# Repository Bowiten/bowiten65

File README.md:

# bowiten65
a 65% keyboard pcb with a jst connector for a [unified daughterboard](https://github.com/Unified-Daughterboard/Unified-Daughterboard)
# layout

# kicad renders

# production
i have sent this to jlcpcb to make, although it hasn't arrived yet, so use at your own risk

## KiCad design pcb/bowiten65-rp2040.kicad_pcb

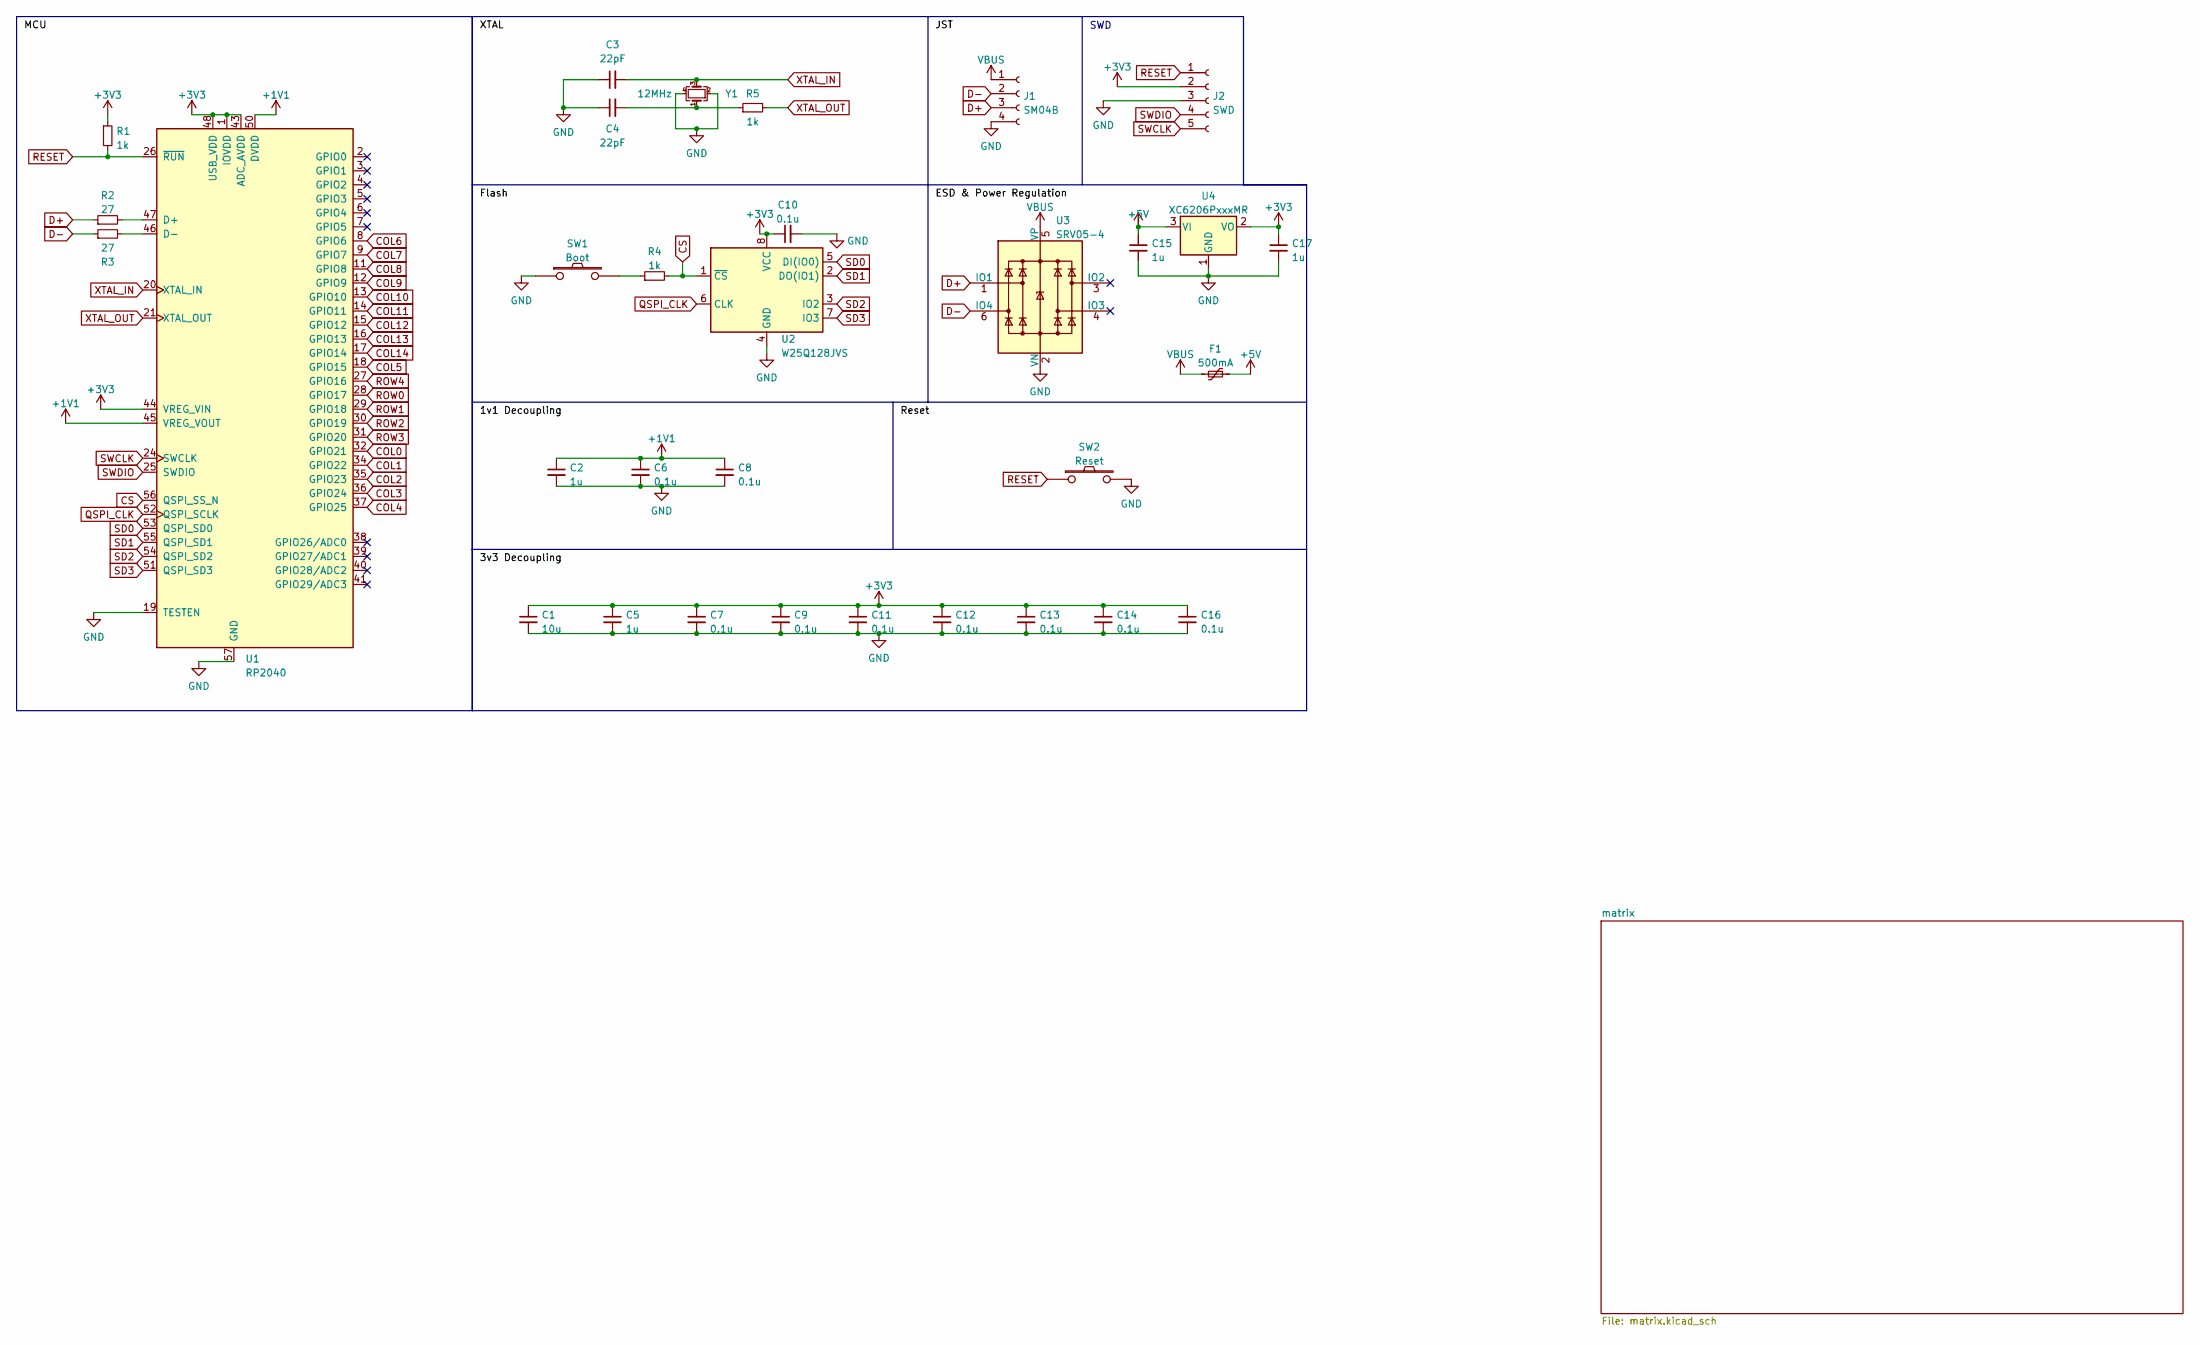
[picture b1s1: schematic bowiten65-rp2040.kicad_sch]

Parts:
C1: 10u; C_0402_1005Metric
C2, C5, C15, C17: 1u; C_0402_1005Metric
C3, C4: 22pF; C_0402_1005Metric
C6, C7, C8, C9, C10, C11, C12, C13, C14, C16: 0.1u; C_0402_1005Metric
F1: 500mA; Fuse_1206_3216Metric
J1: SM04B; JST_SH_SM04B-SRSS-TB_1x04-1MP_P1.00mm_Horizontal
J2: SWD; PinSocket_1x05_P2.54mm_Vertical
R1, R4, R5: 1k; R_0402_1005Metric
R2, R3: 27; R_0603_1608Metric
SW1: Boot; SW_SPST_TL3342
SW2: Reset; SW_SPST_TL3342
U1: RP2040; RP2040-QFN-56; LCSC C2040
U2: W25Q128JVS; SOIC-8_5.23x5.23mm_P1.27mm
U3: SRV05-4; SOT-23-6-routable
U4: XC6206PxxxMR; SOT-23
Y1: 12MHz; Crystal_SMD_3225-4Pin_3.2x2.5mm

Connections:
+1V1: C2.1, C6.1, C8.1, U1.23 (DVDD), U1.45 (VREG_VOUT), U1.50 (DVDD)
+3V3: C1.1, C5.1, C7.1, C9.1, C10.1, C11.1, C12.1, C13.1, C14.1, C16.1, C17.1, J2.2, R1.1, U1.1 (IOVDD), U1.10 (IOVDD), U1.22 (IOVDD), U1.33 (IOVDD), U1.42 (IOVDD), U1.43 (ADC_AVDD), U1.44 (VREG_VIN), U1.48 (USB_VDD), U1.49 (IOVDD), U2.8 (VCC), U4.2 (VO)
+5V: C15.1, F1.1, U4.3 (VI)
COL0: U1.32 (GPIO21); also elsewhere on the board
COL1: U1.34 (GPIO22); also elsewhere on the board
COL2: U1.35 (GPIO23); also elsewhere on the board
COL3: U1.36 (GPIO24); also elsewhere on the board
COL4: U1.37 (GPIO25); also elsewhere on the board
COL5: U1.18 (GPIO15); also elsewhere on the board
COL6: U1.8 (GPIO6); also elsewhere on the board
COL7: U1.9 (GPIO7); also elsewhere on the board
COL8: U1.11 (GPIO8); also elsewhere on the board
COL9: U1.12 (GPIO9); also elsewhere on the board
COL10: U1.13 (GPIO10); also elsewhere on the board
COL11: U1.14 (GPIO11); also elsewhere on the board
COL12: U1.15 (GPIO12); also elsewhere on the board
COL13: U1.16 (GPIO13); also elsewhere on the board
COL14: U1.17 (GPIO14); also elsewhere on the board
CS: R4.2, U1.56 (QSPI_SS_N), U2.1 (~CS)
D+: J1.3, R2.1, U3.1 (IO1)
D-: J1.2, R3.1, U3.6 (IO4)
GND: C1.2, C2.2, C3.1, C4.1, C5.2, C6.2, C7.2, C8.2, C9.2, C10.2, C11.2, C12.2, C13.2, C14.2, C15.2, C16.2, C17.2, J1.4, J2.3, SW1.1, SW2.2, U1.19 (TESTEN), U1.57 (GND), U2.4 (GND), U3.2 (VN), U4.1 (GND), Y1.2, Y1.4
unnamed: C4.2, R5.1, Y1.1
unnamed: R2.2, U1.47 (D+)
unnamed: R3.2, U1.46 (D-)
unnamed: R4.1, SW1.2
QSPI_CLK: U1.52 (QSPI_SCLK), U2.6 (CLK)
RESET: J2.1, R1.2, SW2.1, U1.26 (~RUN)
ROW0: U1.28 (GPIO17); also elsewhere on the board
ROW1: U1.29 (GPIO18); also elsewhere on the board
ROW2: U1.30 (GPIO19); also elsewhere on the board
ROW3: U1.31 (GPIO20); also elsewhere on the board
ROW4: U1.27 (GPIO16); also elsewhere on the board
SD0: U1.53 (QSPI_SD0), U2.5 (DI(IO0))
SD1: U1.55 (QSPI_SD1), U2.2 (DO(IO1))
SD2: U1.54 (QSPI_SD2), U2.3 (IO2)
SD3: U1.51 (QSPI_SD3), U2.7 (IO3)
SWCLK: J2.5, U1.24 (SWCLK)
SWDIO: J2.4, U1.25 (SWDIO)
VBUS: F1.2, J1.1, U3.5 (VP)
XTAL_IN: C3.2, U1.20 (XTAL_IN), Y1.3
XTAL_OUT: R5.2, U1.21 (XTAL_OUT)

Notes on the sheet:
SWD

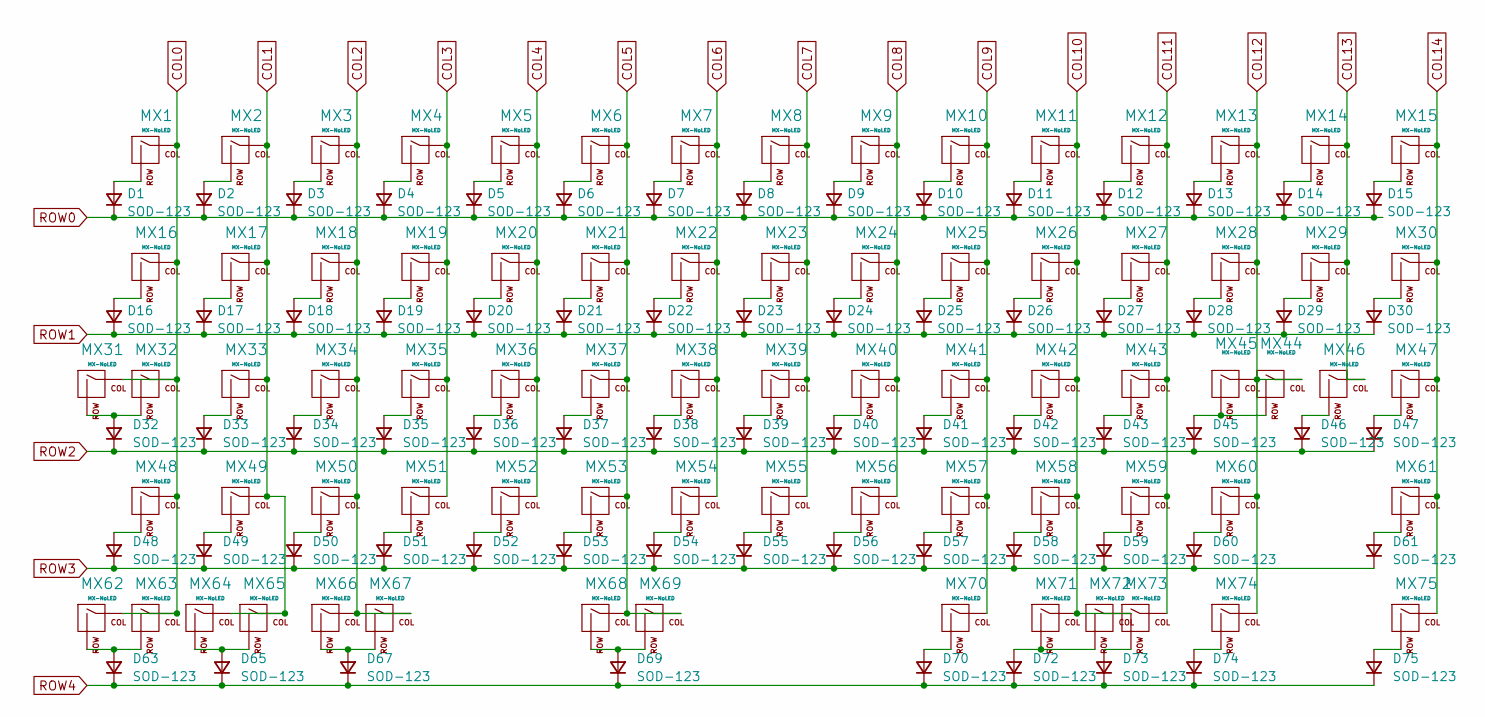
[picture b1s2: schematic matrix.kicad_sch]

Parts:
D1, D2, D3, D4, D5, D6, D7, D8, D9, D10, D11, D12, D13, D14, D15, D16, D17, D18, D19, D20, D21, D22, D23, D24, D25, D26, D27, D28, D29, D30, D32, D33, D34, D35, D36, D37, D38, D39, D40, D41, D42, D43, D45, D46, D47, D48, D49, D50, D51, D52, D53, D54, D55, D56, D57, D58, D59, D60, D61, D63, D65, D67, D69, D70, D72, D73, D74, D75: SOD-123; D_SOD-123; LCSC C33221
MX1, MX2, MX3, MX4, MX5, MX6, MX7, MX8, MX9, MX10, MX11, MX12, MX13, MX15, MX17, MX18, MX19, MX20, MX21, MX22, MX23, MX24, MX25, MX26, MX27, MX28, MX30, MX33, MX34, MX35, MX36, MX37, MX38, MX39, MX40, MX41, MX42, MX43, MX44, MX47, MX49, MX50, MX51, MX52, MX53, MX54, MX55, MX56, MX57, MX58, MX60, MX61, MX65, MX73, MX74, MX75: MX-NoLED; MXOnly-1U-NoLED
MX14: MX-NoLED; MXOnly-2U-NoLED
MX16, MX29, MX63, MX67, MX71: MX-NoLED; MXOnly-1.5U-NoLED
MX31, MX46, MX62, MX64, MX66, MX70, MX72: MX-NoLED; MXOnly-1.25U-NoLED
MX32, MX59: MX-NoLED; MXOnly-1.75U-NoLED
MX45, MX48: MX-NoLED; MXOnly-2.25U-NoLED
MX68: MX-NoLED; MXOnly-6.25U-ReversedStabilizers-NoLED
MX69: MX-NoLED; MXOnly-7U-ReversedStabilizers-NoLED

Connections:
COL0: MX1.1 (COL), MX16.1 (COL), MX31.1 (COL), MX32.1 (COL), MX48.1 (COL), MX62.1 (COL), MX63.1 (COL); also elsewhere on the board
COL1: MX2.1 (COL), MX17.1 (COL), MX33.1 (COL), MX49.1 (COL), MX64.1 (COL), MX65.1 (COL); also elsewhere on the board
COL2: MX3.1 (COL), MX18.1 (COL), MX34.1 (COL), MX50.1 (COL), MX66.1 (COL), MX67.1 (COL); also elsewhere on the board
COL3: MX4.1 (COL), MX19.1 (COL), MX35.1 (COL), MX51.1 (COL); also elsewhere on the board
COL4: MX5.1 (COL), MX20.1 (COL), MX36.1 (COL), MX52.1 (COL); also elsewhere on the board
COL5: MX6.1 (COL), MX21.1 (COL), MX37.1 (COL), MX53.1 (COL), MX68.1 (COL), MX69.1 (COL); also elsewhere on the board
COL6: MX7.1 (COL), MX22.1 (COL), MX38.1 (COL), MX54.1 (COL); also elsewhere on the board
COL7: MX8.1 (COL), MX23.1 (COL), MX39.1 (COL), MX55.1 (COL); also elsewhere on the board
COL8: MX9.1 (COL), MX24.1 (COL), MX40.1 (COL), MX56.1 (COL); also elsewhere on the board
COL9: MX10.1 (COL), MX25.1 (COL), MX41.1 (COL), MX57.1 (COL), MX70.1 (COL); also elsewhere on the board
COL10: MX11.1 (COL), MX26.1 (COL), MX42.1 (COL), MX58.1 (COL), MX71.1 (COL), MX72.1 (COL); also elsewhere on the board
COL11: MX12.1 (COL), MX27.1 (COL), MX43.1 (COL), MX59.1 (COL), MX73.1 (COL); also elsewhere on the board
COL12: MX13.1 (COL), MX28.1 (COL), MX44.1 (COL), MX45.1 (COL), MX60.1 (COL), MX74.1 (COL); also elsewhere on the board
COL13: MX14.1 (COL), MX29.1 (COL), MX46.1 (COL); also elsewhere on the board
COL14: MX15.1 (COL), MX30.1 (COL), MX47.1 (COL), MX61.1 (COL), MX75.1 (COL); also elsewhere on the board
unnamed: D1.2 (A), MX1.2 (ROW)
unnamed: D2.2 (A), MX2.2 (ROW)
unnamed: D3.2 (A), MX3.2 (ROW)
unnamed: D4.2 (A), MX4.2 (ROW)
unnamed: D5.2 (A), MX5.2 (ROW)
unnamed: D6.2 (A), MX6.2 (ROW)
unnamed: D7.2 (A), MX7.2 (ROW)
unnamed: D8.2 (A), MX8.2 (ROW)
unnamed: D9.2 (A), MX9.2 (ROW)
unnamed: D10.2 (A), MX10.2 (ROW)
unnamed: D11.2 (A), MX11.2 (ROW)
unnamed: D12.2 (A), MX12.2 (ROW)
unnamed: D13.2 (A), MX13.2 (ROW)
unnamed: D14.2 (A), MX14.2 (ROW)
unnamed: D15.2 (A), MX15.2 (ROW)
unnamed: D16.2 (A), MX16.2 (ROW)
unnamed: D17.2 (A), MX17.2 (ROW)
unnamed: D18.2 (A), MX18.2 (ROW)
unnamed: D19.2 (A), MX19.2 (ROW)
unnamed: D20.2 (A), MX20.2 (ROW)
unnamed: D21.2 (A), MX21.2 (ROW)
unnamed: D22.2 (A), MX22.2 (ROW)
unnamed: D23.2 (A), MX23.2 (ROW)
unnamed: D24.2 (A), MX24.2 (ROW)
unnamed: D25.2 (A), MX25.2 (ROW)
unnamed: D26.2 (A), MX26.2 (ROW)
unnamed: D27.2 (A), MX27.2 (ROW)
unnamed: D28.2 (A), MX28.2 (ROW)
unnamed: D29.2 (A), MX29.2 (ROW)
unnamed: D30.2 (A), MX30.2 (ROW)
unnamed: D32.2 (A), MX31.2 (ROW), MX32.2 (ROW)
unnamed: D33.2 (A), MX33.2 (ROW)
unnamed: D34.2 (A), MX34.2 (ROW)
unnamed: D35.2 (A), MX35.2 (ROW)
unnamed: D36.2 (A), MX36.2 (ROW)
unnamed: D37.2 (A), MX37.2 (ROW)
unnamed: D38.2 (A), MX38.2 (ROW)
unnamed: D39.2 (A), MX39.2 (ROW)
unnamed: D40.2 (A), MX40.2 (ROW)
unnamed: D41.2 (A), MX41.2 (ROW)
unnamed: D42.2 (A), MX42.2 (ROW)
unnamed: D43.2 (A), MX43.2 (ROW)
unnamed: D45.2 (A), MX44.2 (ROW), MX45.2 (ROW)
unnamed: D46.2 (A), MX46.2 (ROW)
unnamed: D47.2 (A), MX47.2 (ROW)
unnamed: D48.2 (A), MX48.2 (ROW)
unnamed: D49.2 (A), MX49.2 (ROW)
unnamed: D50.2 (A), MX50.2 (ROW)
unnamed: D51.2 (A), MX51.2 (ROW)
unnamed: D52.2 (A), MX52.2 (ROW)
unnamed: D53.2 (A), MX53.2 (ROW)
unnamed: D54.2 (A), MX54.2 (ROW)
unnamed: D55.2 (A), MX55.2 (ROW)
unnamed: D56.2 (A), MX56.2 (ROW)
unnamed: D57.2 (A), MX57.2 (ROW)
unnamed: D58.2 (A), MX58.2 (ROW)
unnamed: D59.2 (A), MX59.2 (ROW)
unnamed: D60.2 (A), MX60.2 (ROW)
unnamed: D61.2 (A), MX61.2 (ROW)
unnamed: D63.2 (A), MX62.2 (ROW), MX63.2 (ROW)
unnamed: D65.2 (A), MX64.2 (ROW), MX65.2 (ROW)
unnamed: D67.2 (A), MX66.2 (ROW), MX67.2 (ROW)
unnamed: D69.2 (A), MX68.2 (ROW), MX69.2 (ROW)
unnamed: D70.2 (A), MX70.2 (ROW)
unnamed: D72.2 (A), MX71.2 (ROW), MX72.2 (ROW)
unnamed: D73.2 (A), MX73.2 (ROW)
unnamed: D74.2 (A), MX74.2 (ROW)
unnamed: D75.2 (A), MX75.2 (ROW)
ROW0: D1.1 (K), D2.1 (K), D3.1 (K), D4.1 (K), D5.1 (K), D6.1 (K), D7.1 (K), D8.1 (K), D9.1 (K), D10.1 (K), D11.1 (K), D12.1 (K), D13.1 (K), D14.1 (K), D15.1 (K); also elsewhere on the board
ROW1: D16.1 (K), D17.1 (K), D18.1 (K), D19.1 (K), D20.1 (K), D21.1 (K), D22.1 (K), D23.1 (K), D24.1 (K), D25.1 (K), D26.1 (K), D27.1 (K), D28.1 (K), D29.1 (K), D30.1 (K); also elsewhere on the board
ROW2: D32.1 (K), D33.1 (K), D34.1 (K), D35.1 (K), D36.1 (K), D37.1 (K), D38.1 (K), D39.1 (K), D40.1 (K), D41.1 (K), D42.1 (K), D43.1 (K), D45.1 (K), D46.1 (K), D47.1 (K); also elsewhere on the board
ROW3: D48.1 (K), D49.1 (K), D50.1 (K), D51.1 (K), D52.1 (K), D53.1 (K), D54.1 (K), D55.1 (K), D56.1 (K), D57.1 (K), D58.1 (K), D59.1 (K), D60.1 (K), D61.1 (K); also elsewhere on the board
ROW4: D63.1 (K), D65.1 (K), D67.1 (K), D69.1 (K), D70.1 (K), D72.1 (K), D73.1 (K), D74.1 (K), D75.1 (K); also elsewhere on the board

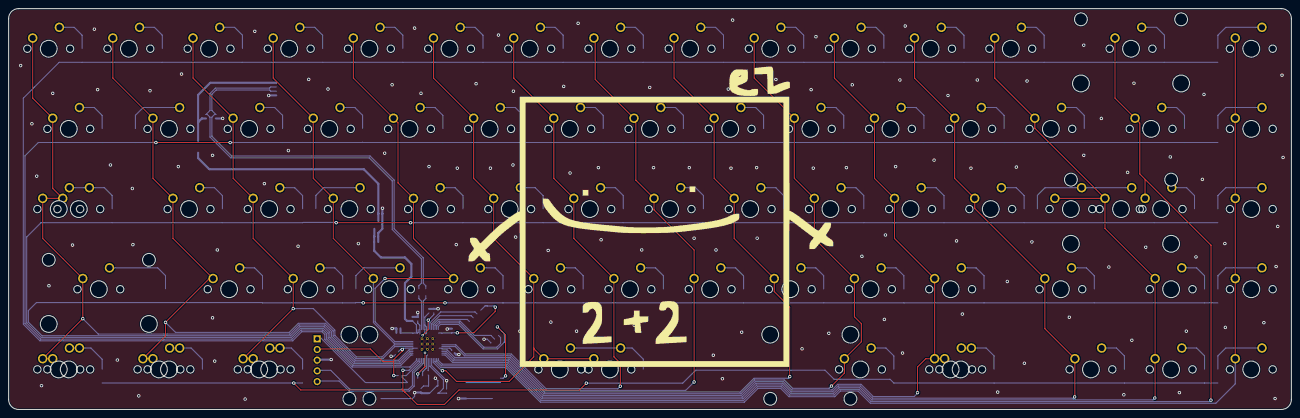
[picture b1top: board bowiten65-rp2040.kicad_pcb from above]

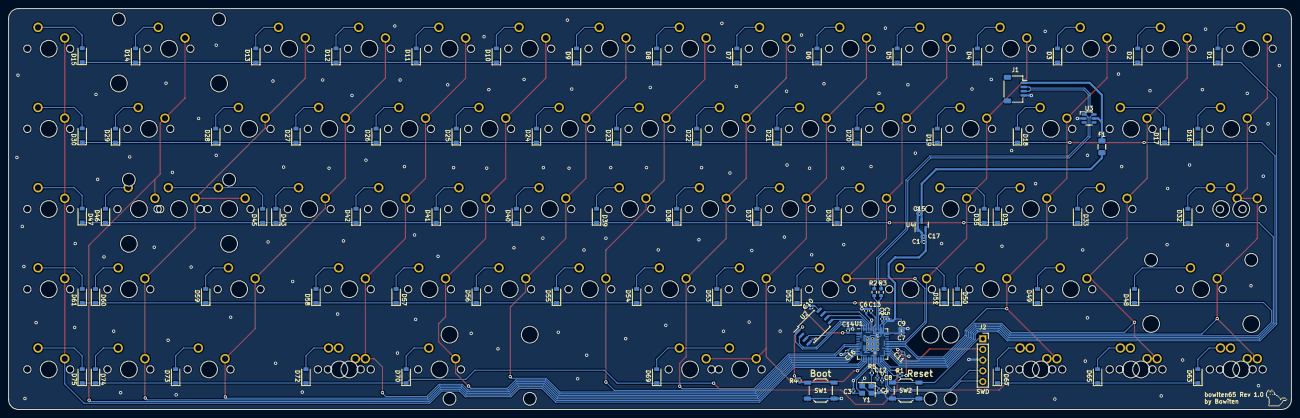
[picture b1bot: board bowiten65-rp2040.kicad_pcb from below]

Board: 2 copper layers, 304.8 x 95.2 mm, 175 parts (100 on the bottom side), 110 nets.

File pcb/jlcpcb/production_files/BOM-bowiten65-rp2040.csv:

Comment,Designator,Footprint,LCSC
1k,"R1,R4,R5",R_0402_1005Metric,C11702
0.1u,"C10,C11,C12,C13,C14,C16,C6,C7,C8,C9",C_0402_1005Metric,C1525
10u,C1,C_0402_1005Metric,C15525
22pF,"C3,C4",C_0402_1005Metric,C1555
SM04B,J1,JST_SH_SM04B-SRSS-TB_1x04-1MP_P1.00mm_Horizontal,C160404
RP2040,U1,RP2040-QFN-56,C2040
27,"R2,R3",R_0603_1608Metric,C25190
Boot,"SW1,SW2",SW_SPST_TL3342,C318884
1u,"C15,C17,C2,C5",C_0402_1005Metric,C52923
XC6206PxxxMR,U4,SOT-23,C5446
500mA,F1,Fuse_1206_3216Metric,C70077
SOD-123,"D1,D10,D11,D12,D13,D14,D15,D16,D17,D18,D19,D2,D20,D21,D22,D23,D24,D25,D26,D27,D28,D29,D3,D30,D32,D33,D34,D35,D36,D37,D38,D39,D4,D40,D41,D42,D43,D45,D46,D47,D48,D49,D5,D50,D51,D52,D53,D54,D55,D56,D57,D58,D59,D6,D60,D61,D63,D65,D67,D69,D7,D70,D72,D73,D74,D75,D8,D9",D_SOD-123,C81598
SRV05-4,U3,SOT-23-6-routable,C85364
12MHz,Y1,Crystal_SMD_3225-4Pin_3.2x2.5mm,C9002
W25Q128JVS,U2,SOIC-8_5.23x5.23mm_P1.27mm,C97521

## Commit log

2023-01-08 yeah
